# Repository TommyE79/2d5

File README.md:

# Reverse engineering 5D mark II (5D2) image sensor

This repository contains notes tools for reverse engineering the image sensor of the Canon EOS 5D mark II
DSLR. The image sensor is relatively cheap available (~80$) and has a "full frame" sized active area
(36mm × 24mm) with 5,616px × 3,744px (21.0 MP). The 5D mark II important in popularizing DSLR cameras
for video making and the Magic Lantern firmware was originally written for this camera.

## Connectors

The sensor has 3 connectors:

* larger stacking 20*2 position connector 
* smaller stacking 15*2 position connector 
* other 4 position connector probably going to the vibration cleaning of the sensor

The stacking connectors have the same pitch (0.466mm - 0.475mm measured probably 0.5mm) and are likely of the same series.
Mating height is ~1.5mm.

* Panasonic AXK5F should be fitting (probably original) [see Datasheet for details](interesting_datasheets/discon2013e_p5kf.pdf)
  * AXK5F ==> Socket
  * AXK6F ==> Header
* TXGA FBB05001-F40S1003W5M / FBB05001-M40S1013W5M should fit (but is hard to obtain)
* Atom-connector BTB050040-F1S03201 / BTB050040-M1S03201 should fit
* XKB Connectivity X0511FVS-40B-LPV01 / X0511WVS-40A-LPV01 should fit and is on lcsc

A breakout board for intercepting communications between the camera and the sensor can be found
in the [connector_breakout](connector/breakout) directory. It fits onto the mainboard and adapts the
connectors to 0.1" headers.

## Pinout

To this point only static analysis of the pinout has been done. The results of this can be found in
the [connector pinouts table](connector_pinouts.ods). To obtain the results in the table
a warm round of guesswork guided by a multimeter and some PCB tracing (see gimp files in `pictures/`)
have been used. During the probing it was immensely helpful to have the breakout PCBs ordered with
white silkscreen to be able to write results directly to the breakout boards.

The sensor most likely outputs its analog data using differential pairs and requires
a bunch of different power supplies. To get a glimpse on how the interface could look like, see the
[datasheet of the Cypress IBIS4-14000](interesting_datasheets/Cypress_Semiconductor-IBIS4-14000-M-datasheet.pdf).

The next step is to probe the sensor in-camera with a logic analyser / oscilloscope / multimeter to
obtain information about the power supply rails, the exact pinout and the scheme of driving the
sensor. Some basic testing was with a logic analyser was done and the traces can be found in the traces directory.

## Readout

The 5d2 sensor outputs analog values (no on chip ADC) with 4 channel readout.

Required sample rates (purely theoretical):

| Format          | resolution | framerate | pixel rate / 4 [Mpix/s] |
| :-------------- | :--------- | :-------- | :---------------------- |
| FHD             | 1920x1080  | 24        | 12.4416                 |
| FHD             | 1920x1080  | 30        | 15.552                  |
| HALF 16:9       | 2808x1580  | 24        | 26.61984                |
| FHD             | 1920x1080  | 60        | 31.104                  |
| HALF            | 2808x1872  | 24        | 31.53945                |
| HALF 16:9       | 2808x1580  | 30        | 33.2748                 |
| HALF            | 2808x1872  | 30        | 39.42432                |
| camera 1080p    | 5568x1044  | 30        | 43.59744                |
| FULL 3-lineskip | 5568x1248  | 30        | 52.11648                |
| 4k 16:9 (CROP)  | 4096x2304  | 24        | 56.62310                |
| HALF 16:9       | 2808x1580  | 60        | 66.5496                 |
| 4k 16:9 (CROP)  | 4096x2304  | 30        | 70.77888                |
| HALF            | 2808x1872  | 60        | 78.84864                |
| FULL 21:9       | 5616x2407  | 24        | 81.10627                |
| FULL 21:9       | 5616x2407  | 30        | 101.3828                |
| FULL 16:9       | 5616x3159  | 24        | 106.4456                |
| FULL            | 5616x3744  | 24        | 126.1578                |
| FULL 16:9       | 5616x3159  | 30        | 133.0570                |
| 4k 16:9 (CROP)  | 4096x2304  | 60        | 141.5577                |
| FULL            | 5616x3744  | 30        | 157.6972                |

Notes:

* The camera is [reported to use a column 3x binning and row 3x skipping](https://www.magiclantern.fm/forum/index.php?topic=16516.0)
  in its video mode. The FHD mode seems to use on-chip row and column skipping and a slightly-less than FHD readout with digital upscaling
  for the FHD video output. The readout clock used in the camera is ~24Mhz.
* It is unclear if row / column subsampling is possible with the sensor interface (concerns HALF, FHD and CROP modes)
* 4k DCI would have a crop factor of 1.371 (vs 1.6 for APSC)
* USB 3.0 can theoretically transport 500Mbyte/s as a theoretical maximum and probably not much more than 400Mbyte/s in practice.

some possible ADCs:
| part          | channels | sample rate [Msa/s] | bit depth | price   | notes                                    |
| :------------ | :------- | :------------------ | :-------- | :------ | :--------------------------------------- |
| VSP5622       | 4        | 70                  | 16        | 14$     | obsolete                                 |
| ADDI7004BBBCZ | 4        | 72                  | 14        | 65$     |                                          |
| ADC34J45IRGZR | 4        | 160                 | 14        | 81$     | only ADC                                 |
| ADC3244       | 2        | 125                 | 14        | 26$ @1k | only ADC                                 |
| HMCAD1520     | 4        | 160                 | 12        | 121$    | only ADC; possibly same die as HMCAD1511 |
| HMCAD1511     | 4        | 125                 | 8         | 13$     | only ADC; possibly same die as HMCAD1511 |

There is a test-board with a HMCAD1511 in the [zynq-test-board/](zynq-test-board/) folder.

# Analog output

The image sensor outputs at four channels differentially. after each pixel, the differential output
goes to 0mV differential value (maybe blacklevel compensation).
Each side (positive and negative) is centered at ~1.4V and has 300-400mv Swing. The differential
values range from -600mV to +600mV.

## WiP -- Back engineering the Sensor connector board for deeper understanding of functinality

Started an KiCad based back engineered schematic from the detail photos

The schematic wwill be in [senor_board_back_engineered](connector_breakout/senor_board_back_engineered/) folder.

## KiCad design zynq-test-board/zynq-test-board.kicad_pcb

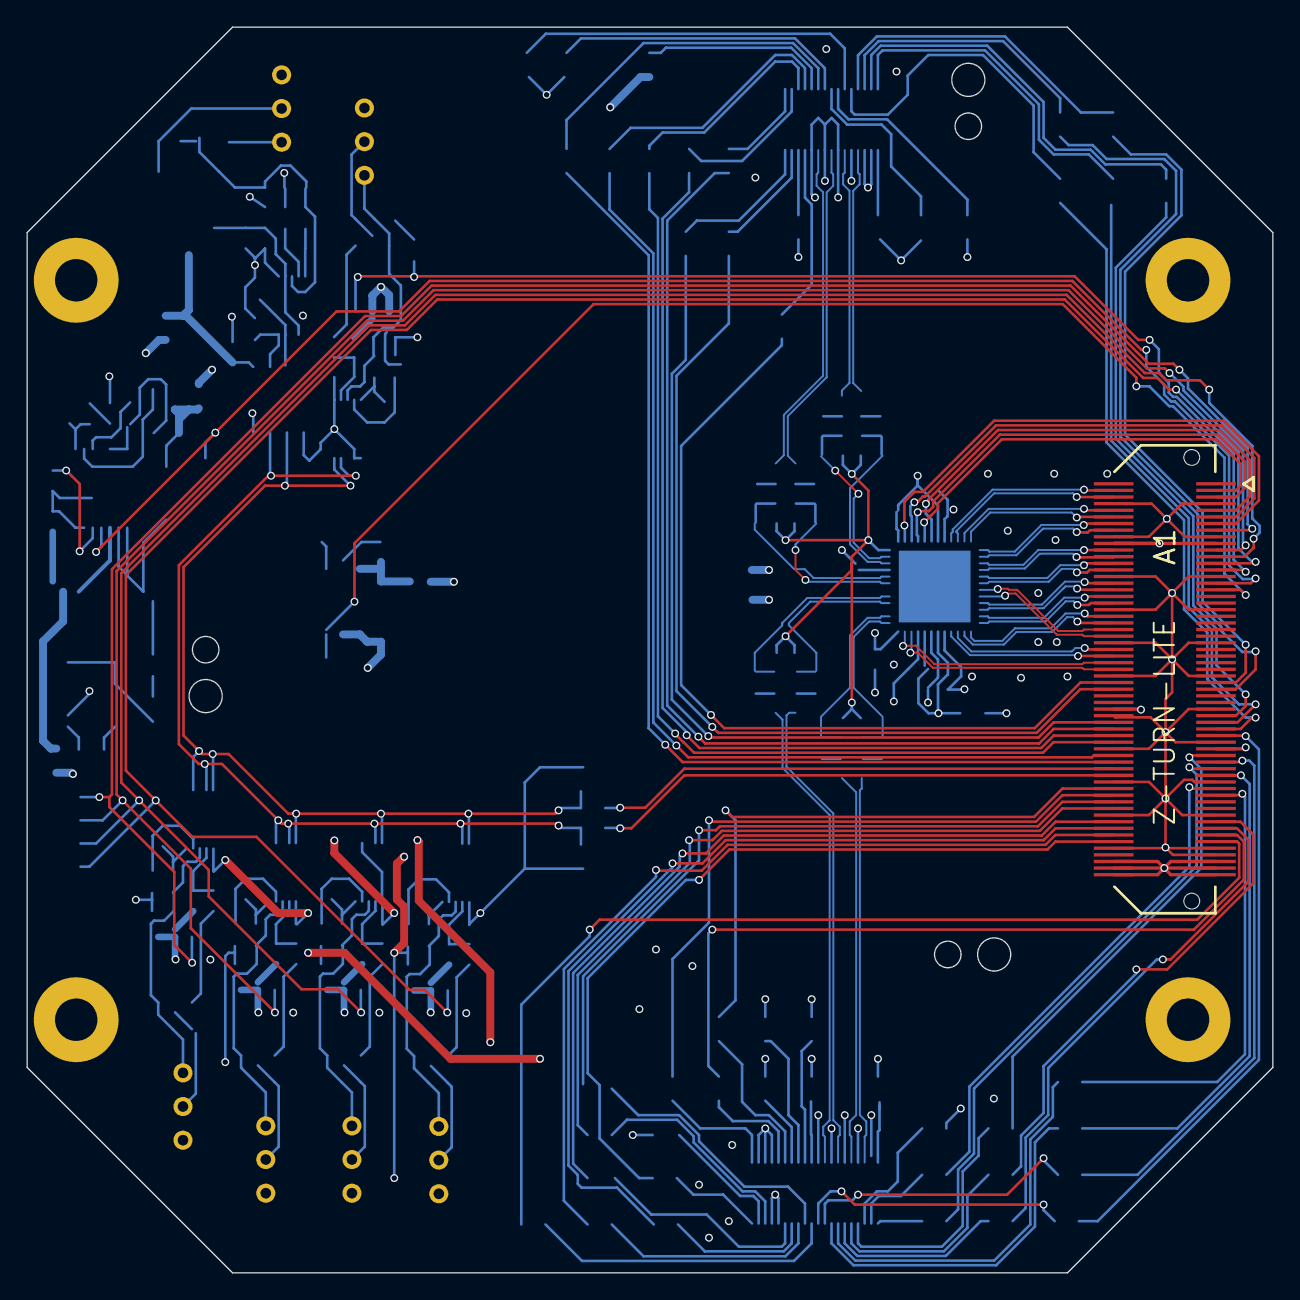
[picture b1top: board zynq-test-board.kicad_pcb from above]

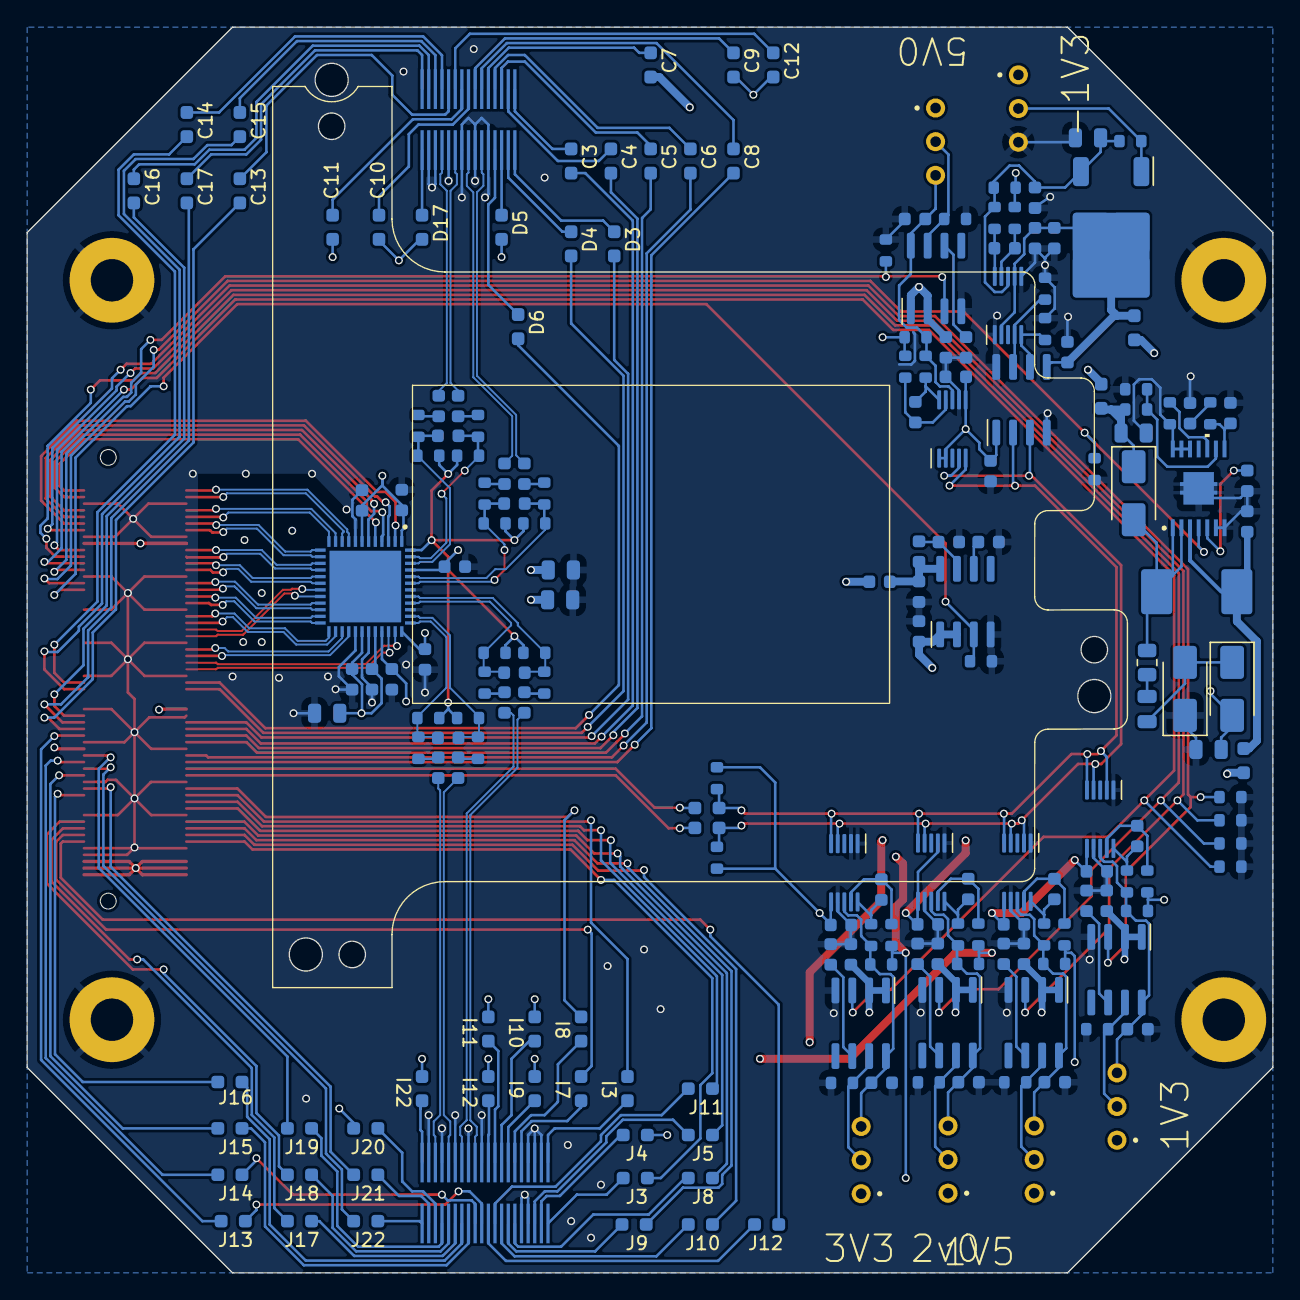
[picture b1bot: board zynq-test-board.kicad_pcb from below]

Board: 4 copper layers, 94.0 x 94.0 mm, 206 parts (201 on the bottom side), 199 nets.

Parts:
A1: Z-TURN-LITE; CONN_BTH-060-XX-X-D-LC
A2: 2d5_flat
C1, C3, C6, C8, C14, C16, C22, C24, C30, C32, C35, C42, C44, C47, C49: 1u; C_0603_1608Metric
C2, C7, C9, C10, C15, C17, C18, C23, C25, C26, C31, C33, C34, C36, C37, C43, C45, C46, C50, C51, C54, C55, C56, C57, C59, C60, C64, C65, C66: 0.1u; C_0603_1608Metric
C11, C12, C19, C20, C27, C28, C61, C62: 100n; C_0603_1608Metric
C13, C21, C29, C63: 22pF; C_0603_1608Metric
C38: 100p; C_0603_1608Metric
C39, C40, C41, C48, C52, C53, C58: 10u; C_0805_2012Metric
D1, D2, D3: D_Schottky; D_SMA
H1, H2, H3, H4: MountingHole_Pad; MountingHole_3.2mm_M3_Pad
L1: 10u; L_Abracon_ASPI-0630LR
R1: 0; C_0603_1608Metric
R2, R43: 10k; R_0603_1608Metric
R3, R4, R5: 22k; R_0603_1608Metric
R6: 6k8; R_0603_1608Metric
R7: 8k2; C_0603_1608Metric
R8: 27k; C_0603_1608Metric
R9, R10, R11, R19, R27, R35, R44, R48, R59, R60, R61, R62, R95, R96, R97, R98, R108, R109, R110: 0; R_0603_1608Metric_Pad0.98x0.95mm_HandSolder
R12, R20, R28, R36, R45, R50: 10m; R_0603_1608Metric
R13, R14, R21, R22, R29, R30, R37, R38, R46, R47, R51, R52: 10; R_0603_1608Metric
R15, R16, R23, R24, R31, R32, R55, R56: 22; R_0603_1608Metric
R17, R18, R25, R26, R33, R34, R57, R58: 1k; R_0603_1608Metric
R39: 40k; R_0603_1608Metric
R40: 2.55k; R_0603_1608Metric
R41: 1R; R_0805_2012Metric
R42: 39k; R_0603_1608Metric
R49: 47k; R_0603_1608Metric
R53, R54, R99, R100, R101, R102, R103, R104, R105, R106, R107: 4k7; R_0603_1608Metric
R63, R64, R65, R66, R67, R68, R69, R70, R71, R72, R73, R74, R75, R76, R77, R78, R79, R80, R81, R82, R83, R84, R85, R86, R87, R88, R89, R90, R91, R92, R93, R94: 220; R_0603_1608Metric_Pad0.98x0.95mm_HandSolder
RV2, RV3, RV4, RV5, RV6, RV7: 100k; Potentiometer_Bourns_3296W_Vertical
U1, U3, U5, U7, U9, U12: MCP1727-ADJxSN; SOIC-8_3.9x4.9mm_P1.27mm
U4, U6, U8, U10, U13, U16: INA226; VSSOP-10_3x3mm_P0.5mm
U11: TPS55340PWPR; PWP14
U15: LM337_TO252; TO-252-2
U17: ISO1541; SOIC-8_3.9x4.9mm_P1.27mm
U18: HMCAD1511; QFN_48_ADI

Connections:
+2V5: A1.19 (VDDIO_35_PL), A1.20 (VDDIO_35_PL), C22.1, C30.1, C53.1, C55.1, U7.1 (Vin), U7.2 (Vin), U9.1 (Vin), U9.2 (Vin), U18.33 (OVDD)
+3V3: A1.70 (VDDIO_34_PL), A1.81 (VDDIO_34_PL), C1.1, C10.1, C14.1, C18.1, C26.1, C34.1, C46.1, C65.1, R99.1, R100.1, U1.1 (Vin), U1.2 (Vin), U4.6 (VS), U5.1 (Vin), U5.2 (Vin), U6.2 (A0), U6.6 (VS), U8.6 (VS), U10.6 (VS), U13.1 (A1), U13.2 (A0), U13.6 (VS), U17.1 (VCC1)
+5V: A1.115 (VDD_5V), A1.116 (VDD_5V), A1.117 (VDD_5V), A1.118 (VDD_5V), A1.119 (VDD_5V), A1.120 (VDD_5V), C6.1, R110.1, U3.1 (Vin), U3.2 (Vin)
/ADC/A1+: A2.D12 (A2+), C20.1
/ADC/A1-: A2.D14 (A2-), C19.1
/ADC/A2+: A2.D8 (A1+), C12.1
/ADC/A2-: A2.D10 (A1-), C11.1
/ADC/A3+: A2.I14 (A3+), C62.1
/ADC/A3-: A2.I16 (A3-), C61.1
/ADC/A4+: A2.I18 (A4+), C28.1
/ADC/A4-: A2.I20 (A4-), C27.1
/ADC/ADC_CSN: A1.13 (IO_B35_LP16), U18.2 (CSN)
/ADC/ADC_PD: A1.9 (IO_B35_LP5), U18.6 (PD)
/ADC/ADC_SCLK: A1.5 (IO_B35_LN2), U18.4 (SCLK)
/ADC/ADC_SDATA: A1.11 (IO_B35_LN5), U18.3 (SDATA)
/ADC/CLK+: A1.56 (IO_B35_LP23), U18.35 (CLKP)
/ADC/CLK-: A1.58 (IO_B35_LN23), U18.34 (CLKN)
/ADC/D1A+: A1.4 (IO_B35_LP3), U18.9 (DP1A)
/ADC/D1A-: A1.6 (IO_B35_LN3), U18.10 (DN1A)
/ADC/D1B+: A1.10 (IO_B35_LP4), U18.11 (DP1B)
/ADC/D1B-: A1.12 (IO_B35_LN4), U18.12 (DN1B)
/ADC/D2A+: A1.14 (IO_B35_LP6), U18.13 (DP2A)
/ADC/D2A-: A1.16 (IO_B35_LN6), U18.14 (DN2A)
/ADC/D2B+: A1.22 (IO_B35_LP17), U18.15 (DP2B)
/ADC/D2B-: A1.24 (IO_B35_LN17), U18.16 (DN2B)
/ADC/D3A+: A1.32 (IO_B35_LP10), U18.21 (DP3A)
/ADC/D3A-: A1.34 (IO_B35_LN10), U18.22 (DN3A)
/ADC/D3B+: A1.36 (IO_B35_LP19), U18.23 (DP3B)
/ADC/D3B-: A1.38 (IO_B35_LN19), U18.24 (DN3B)
/ADC/D4A+: A1.42 (IO_B35_LP20), U18.25 (DP4A)
/ADC/D4A-: A1.44 (IO_B35_LN20), U18.26 (DN4A)
/ADC/D4B+: A1.52 (IO_B35_LP22), U18.27 (DP4B)
/ADC/D4B-: A1.54 (IO_B35_LN22), U18.28 (DN4B)
/ADC/FCLK+: A1.46 (IO_B35_LP13), U18.19 (FCLKP)
/ADC/FCLK-: A1.48 (IO_B35_LN13), U18.20 (FCLPN)
/ADC/LCLK+: A1.26 (IO_B35_LP12), U18.17 (LCLKP)
/ADC/LCLK-: A1.28 (IO_B35_LN12), U18.18 (LCLKN)
/ADC/filter 1/OUT_N: C21.1, R23.2, R25.1, U18.46 (IN1)
/ADC/filter 1/OUT_P: C21.2, R24.2, R26.2, U18.47 (IP1)
/ADC/filter 2/OUT_N: C13.1, R15.2, R17.1, U18.43 (IN2)
/ADC/filter 2/OUT_P: C13.2, R16.2, R18.2, U18.44 (IP2)
/ADC/filter 3/OUT_N: C63.1, R55.2, R57.1, U18.40 (IN3)
/ADC/filter 3/OUT_P: C63.2, R56.2, R58.2, U18.41 (IP3)
/ADC/filter 4/OUT_N: C29.1, R31.2, R33.1, U18.37 (IN4)
/ADC/filter 4/OUT_P: C29.2, R32.2, R34.2, U18.38 (IP4)
/ADC/~ADC_RESET: A1.3 (IO_B35_LP2), U18.5 (RESETN)
/Power/5v reg/Vin: C35.1, L1.1, R110.2, U11.3 (VIN)
/Power/5v reg/Vout+: C41.1, D1.1 (K), R42.1, R109.1
/Power/5v reg/Vout-: C40.1, D2.2 (A), R108.1
/Power/+6V: C42.1, R109.2, U12.1 (Vin), U12.2 (Vin)
/Power/-6V: C47.1, C51.2, C66.2, R108.2, U15.2 (VI), U16.2 (A0), U16.7 (GND), U17.5 (GND2)
/Power/negative 1v3/SCL_INT: R53.2, U16.5 (SCL), U17.6 (SCL2)
/Power/negative 1v3/SDA_INT: R54.2, U16.4 (SDA), U17.7 (SDA2)
/Power/sensor 1V5/ADJ: R4.1, RV4.2, U7.7 (ADJ)
/Power/sensor 1v3/ADJ: R5.1, RV5.2, U9.7 (ADJ)
/Power/sensor 2V/ADJ: R3.1, RV3.2, U5.7 (ADJ)
/Power/sensor 3V3/ADJ: R2.1, RV2.2, U3.7 (ADJ)
/Power/sensor 5V/ADJ: R6.1, RV6.2, U12.7 (ADJ)
/digital/FRAME_RST: A1.80 (IO_B34_LN15), R82.1
/digital/LINE0: A1.76 (IO_B34_LN19), R81.1
/digital/LINE1: A1.84 (IO_B34_LP16), R83.1
/digital/LINE2: A1.73 (IO_B34_LN13), R84.1
/digital/LINE3: A1.104 (IO_B34_LP17), R85.1
/digital/LINE5: A1.108 (IO_B34_LP8), R87.1
/digital/LINE6: A1.98 (IO_B34_LP18), R88.1
/digital/LINE7: A1.109 (IO_B34_LN7), R89.1
/digital/LINE8: A1.89 (IO_B34_LN12), R90.1
/digital/LINE9: A1.95 (IO_B34_LN22), R91.1
/digital/LINE10: A1.105 (IO_B34_LN10), R92.1
/digital/LINE11: A1.103 (IO_B34_LP10), R93.1
/digital/LINE_EXP: A1.106 (IO_B34_LN17), R86.1
/digital/LINE_RST: A1.93 (IO_B34_LP22), R94.1
/digital/PXCLK_BOT: A1.100 (IO_B34_LN18), R79.1
/digital/PXCLK_TOP: A1.62 (IO_B34_LP24), R80.1
/digital/SCLK: A1.63 (IO_B34_LN23), R64.1
/digital/SCS: A1.71 (IO_B34_LP13), R65.1
/digital/SDATA: A1.61 (IO_B34_LP23), R63.1
/digital/START0: A1.96 (IO_B34_LN21), R74.1
/digital/START1: A1.107 (IO_B34_LP7), R75.1
/digital/START2: A1.94 (IO_B34_LP21), R76.1
/digital/START3: A1.77 (IO_B34_LN14), R77.1
/digital/START4: A1.83 (IO_B34_LP9), R78.1
/digital/ZERO0: A1.75 (IO_B34_LP14), R66.1
/digital/ZERO1: A1.86 (IO_B34_LN16), R67.1
/digital/ZERO2: A1.78 (IO_B34_LP15), R68.1
/digital/ZERO3: A1.74 (IO_B34_LP19), R69.1
/digital/ZERO4: A1.64 (IO_B34_LN24), R70.1
/digital/ZERO5: A1.110 (IO_B34_LN8), R71.1
/digital/ZERO6: A1.85 (IO_B34_LN9), R72.1
/digital/ZERO7: A1.87 (IO_B34_LP12), R73.1
ADC_1v8: C52.1, C54.1, C56.1, C57.1, C58.1, C59.1, C60.1, C64.1, R1.2, U18.1 (AVDD), U18.7 (DVDD), U18.30 (DVDD), U18.32 (AVDD2), U18.36 (AVDD), U18.45 (AVDD)
EN_1V8_ADC: A1.33 (IO_B35_LN18), R107.1, U1.3 (~SHDN)
EN_SNS_1V3: A1.15 (IO_B35_LN16), R104.1, U9.3 (~SHDN)
EN_SNS_1V5: A1.21 (IO_B35_LP14), R103.1, U7.3 (~SHDN)
EN_SNS_2V0: A1.23 (IO_B35_LN14), R102.1, U5.3 (~SHDN)
EN_SNS_3V3: A1.25 (IO_B35_LP1), R101.1, U3.3 (~SHDN)
EN_SNS_5V: A1.27 (IO_B35_LN1), R105.1, U12.3 (~SHDN)
EN_SNS_HV: A1.31 (IO_B35_LP18), R106.1, U11.4 (EN)
GND: A1.7 (DGND), A1.8 (DGND), A1.17 (DGND), A1.18 (DGND), A1.29 (DGND), A1.30 (DGND), A1.39 (DGND), A1.40 (DGND), A1.49 (DGND), A1.50 (DGND), A1.59 (DGND), A1.60 (DGND), A1.69 (DGND), A1.72 (DGND), A1.79 (DGND), A1.82 (DGND), A1.91 (DGND), A1.92 (DGND), A1.101 (DGND), A1.102 (DGND), A1.111 (DGND), A1.112 (DGND), A1.113 (DGND), A2.D7 (GND), A2.D9 (GND), A2.D11 (GND), A2.D13 (GND), A2.D15 (GND), A2.D16 (GND), A2.I4 (GND), A2.I5 (GND), A2.I6 (GND), A2.I13 (GND), A2.I15 (GND), A2.I17 (GND), A2.I19 (GND), A2.I21 (GND), A2.J6 (GND), A2.J7 (GND), C1.2, C2.1, C3.2, C6.2, C7.1, C8.2, C10.2, C14.2, C15.1, C16.2, C18.2, C22.2, C23.1, C24.2, C26.2, C30.2, C31.1, C32.2, C34.2, C35.2, C36.2, C37.2, C38.2, C40.2, C41.2, C42.2, C43.1, C44.2, C46.2, C47.2, C48.2, C49.2, C51.1, C52.2, C53.2, C54.2, C55.2, C56.2, C57.2, C58.2, C59.2, C60.2, C64.2, C65.2, C66.1, D3.1 (K), H1.1, H2.1, H3.1, H4.1, R2.2, R3.2, R4.2, R5.2, R6.2, R8.1, R39.2, R43.2, R53.1, R54.1, R101.2, R102.2, R103.2, R104.2, R105.2, R106.2, R107.2, RV7.3, U1.4 (GND), U3.4 (GND), U4.1 (A1), U4.2 (A0), U4.7 (GND), U5.4 (GND), U6.1 (A1), U6.7 (GND), U7.4 (GND), U8.1 (A1), U8.7 (GND), U9.4 (GND), U10.1 (A1), U10.7 (GND), U11.6 (SYNC), U11.7 (AGND), U11.12 (PGND), U11.13 (PGND), U11.14 (PGND), U11.15 (EPAD), U12.4 (GND), U13.7 (GND), U16.1 (A1), U16.6 (VS), U17.4 (GND1), U17.8 (VCC2), U18.8 (DVSS), U18.29 (DVSS), U18.31 (AVSS2), U18.39 (AVSS), U18.42 (AVSS)
unnamed: A1.90 (IO_B34_LN20), R98.2
unnamed: A1.88 (IO_B34_LP20), R97.2
unnamed: A2.C10 (1V3), R35.2
unnamed: A2.D17 (1V3), R44.2
unnamed: A2.I10 (1V3), R48.2
unnamed: A2.I22 (1V5), R61.2
unnamed: A2.I9 (2V0), R62.2
unnamed: A2.C7 (3V3), R95.2
unnamed: A2.J20 (3V3), R96.2
unnamed: A2.C11 (5V), R10.2
unnamed: A2.D5 (5V), R9.2
unnamed: A2.I11 (5V), R19.2
unnamed: A2.I12 (5V), R27.2
unnamed: A2.J4 (5V), R11.2
unnamed: A2.C9 (-1V3), R59.2
unnamed: A2.C12 (-1V3), R60.2
unnamed: A2.J5 (PXCLK_BOT), R79.2
unnamed: A2.D6 (PXCLK_TOP), R80.2
unnamed: A2.C15 (SCLK), R64.2
unnamed: A2.C16 (SCS), R65.2
unnamed: A2.C14 (SDATA), R63.2
unnamed: A2.C5 (frame_rst), R82.2
unnamed: A2.C3 (line), R81.2
unnamed: A2.C6 (line), R83.2
unnamed: A2.C17 (line), R84.2
unnamed: A2.J8 (line), R85.2
unnamed: A2.J10 (line), R87.2
unnamed: A2.J11 (line), R88.2
unnamed: A2.J12 (line), R89.2
unnamed: A2.J15 (line), R90.2
unnamed: A2.J16 (line), R91.2
unnamed: A2.J17 (line), R92.2
unnamed: A2.J18 (line), R93.2
unnamed: A2.J9 (line_exp), R86.2
unnamed: A2.J21 (line_reset), R94.2
unnamed: A2.I3 (startup), R74.2
unnamed: A2.I7 (startup), R75.2
unnamed: A2.I8 (startup), R76.2
unnamed: A2.J13 (startup), R77.2
unnamed: A2.J19 (startup), R78.2
unnamed: A2.C4 (zero), R68.2
unnamed: A2.C8 (zero), R67.2
unnamed: A2.C13 (zero), R66.2
unnamed: A2.D3 (zero), R69.2
unnamed: A2.D4 (zero), R70.2
unnamed: A2.J3 (zero), R71.2
unnamed: A2.J14 (zero), R72.2
unnamed: A2.J22 (zero), R73.2
unnamed: C11.2, R15.1
unnamed: C12.2, R16.1
unnamed: C19.2, R23.1
unnamed: C20.2, R24.1
unnamed: C27.2, R31.1
unnamed: C28.2, R32.1
unnamed: C37.1, R40.2
unnamed: C39.1, R41.2
unnamed: C61.2, R55.1
unnamed: C62.2, R56.1
unnamed: D1.2 (A), L1.2, R41.1, U11.1 (SW), U11.2 (SW)
unnamed: C39.2, D2.1 (K), D3.2 (A)
unnamed: R7.1, R8.2, U1.7 (ADJ)
unnamed: C2.2, U1.6 (Cdelay)
unnamed: C3.1, R1.1, R7.2, U1.8 (Vout)
unnamed: C7.2, U3.6 (Cdelay)
unnamed: C8.1, R12.1, R13.2, RV2.3, U3.8 (Vout), U4.8 (Vbus)
unnamed: C9.1, R13.1, U4.10 (Vin+)
unnamed: C9.2, R14.2, U4.9 (Vin-)
unnamed: C15.2, U5.6 (Cdelay)
unnamed: C16.1, R20.1, R21.2, RV3.3, U5.8 (Vout), U6.8 (Vbus)
unnamed: C17.1, R21.1, U6.10 (Vin+)
unnamed: C17.2, R22.2, U6.9 (Vin-)
unnamed: C23.2, U7.6 (Cdelay)
unnamed: C24.1, R28.1, R29.2, RV4.3, U7.8 (Vout), U8.8 (Vbus)
unnamed: C25.1, R29.1, U8.10 (Vin+)
unnamed: C25.2, R30.2, U8.9 (Vin-)
unnamed: C31.2, U9.6 (Cdelay)
unnamed: C32.1, R36.1, R37.2, RV5.3, U9.8 (Vout), U10.8 (Vbus)
unnamed: C33.1, R37.1, U10.10 (Vin+)
unnamed: C33.2, R38.2, U10.9 (Vin-)
unnamed: C38.1, R40.1, U11.8 (COMP)
unnamed: R42.2, R43.1, U11.9 (FB)
unnamed: R39.1, U11.10 (FREQ)
unnamed: C36.1, U11.5 (SS)
unnamed: C43.2, U12.6 (Cdelay)
unnamed: C44.1, R45.1, R46.2, RV6.3, U12.8 (Vout), U13.8 (Vbus)
unnamed: C45.1, R46.1, U13.10 (Vin+)
unnamed: C45.2, R47.2, U13.9 (Vin-)
unnamed: R49.1, RV7.2, U15.1 (ADJ)
unnamed: C48.1, C49.1, R49.2, R50.1, R51.2, U15.3 (VO), U16.8 (Vbus)
unnamed: C50.1, R51.1, U16.10 (Vin+)
unnamed: C50.2, R52.2, U16.9 (Vin-)
SCL: R97.1, R100.2, U4.5 (SCL), U6.5 (SCL), U8.5 (SCL), U10.2 (A0), U10.5 (SCL), U13.5 (SCL), U17.2 (SDA1)
SDA: R98.1, R99.2, U4.4 (SDA), U6.4 (SDA), U8.2 (A0), U8.4 (SDA), U10.4 (SDA), U13.4 (SDA), U17.3 (SCL1)
Sensor+1V3: R35.1, R36.2, R38.1, R44.1, R48.1
Sensor+1V5: R28.2, R30.1, R61.1
Sensor+2V: R20.2, R22.1, R62.1
Sensor+3V3: R12.2, R14.1, R95.1, R96.1
Sensor+5V: R9.1, R10.1, R11.1, R19.1, R27.1, R45.2, R47.1
Sensor-1V3: R50.2, R52.1, R59.1, R60.1
VCM: R17.2, R18.1, R25.2, R26.1, R33.2, R34.1, R57.2, R58.1, U18.48 (VCM)

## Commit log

2024-05-03 Sensorboard back-engineering
    -- WiP --
    Sensorboard back-engineering to determin more detailed functionalty
2024-05-03 Update README.md
    branch update
2024-07-17 +3D Model of the Sensor-Board added
    +3D Model of the Sensor-Board added
    Back engeneering of the Sensor board WiP
2024-07-17 update README.MD
    ..+ Datasheet
2025-01-28 3D Models update
    updated the 3D models of the sensor
